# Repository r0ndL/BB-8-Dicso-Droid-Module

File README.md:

# BB-8-Dicso-Droid-Module
Released under CC4 SA NC BY Jim Yu

Disco-Droid 
Released under CC4 SA NC BY Jim Yu

#Introduction
The Disco Droid is an Arduino based module that will mainly provide Visual and Audio Effect for BB-8’s Dome. In order to create visual effects on the dome, more pins were needed that what an ordinary Arduino can provide, as such there was a need to create a module that has integrated output expander in order to accommodate the needs of the dome, and a few more extras for future upgrades. 
The Disco-Droid is capable working alone, or remotely controlled by another Bluetooth 4.0 LE device, it has a total of 32 12-bit PWM outputs, 7 spare analog pins from the Arduino, and 3 Digital I/O pins also from the Arduino, the Module has also integrated a MP3 Playback module that can drive a single 3W speaker. 

Most of all the different parts that was selected for this module has taken into account that many builders wish to make their domes as light as possible, in order to do so the Disco-Droid was design with the smallest off-the-shelf parts and modules in order to conserve on weight and size. The dimensions of the circuit board is just 2 x 3.5 x .7 inches, just slightly longer than your credit card. 

>Released under CC4 SA NC BY Jim Yu

#Roadmap
**V1.0.6 - Current Final Board Design for Version 1**
**Hardware Features**
- 32 PWM Output (Can handle Motors, LEDs, and Servos, etc..)
- 7 Analog Inputs (Can also be used for Digital Outputs)
- 3 Digital Outputs/Inputs
- 3W Speaker Output
- Bluetooth Ready
- Software Features
- Randomized Sound file playing
- 3 Pre-set Visualizer patterns 
- Small compact Code (using only 14% of the Arduino's memory, and 12% buffer memory)

**V1.1.6 - Same Board Design Utilizing Bluetooth remote connectivity**
**Hardware Features**
- Same as V1.0.6
- Software Features
- When left alone, it will follow V1.0.6 program functions
- Bluetooth Feature will be utilized to trigger the Dome light pattern changes, and sounds.

>In order to utilize V1.1.6 features a future Bluetooth Remote will be released to compliment the Disco-Droid Module.

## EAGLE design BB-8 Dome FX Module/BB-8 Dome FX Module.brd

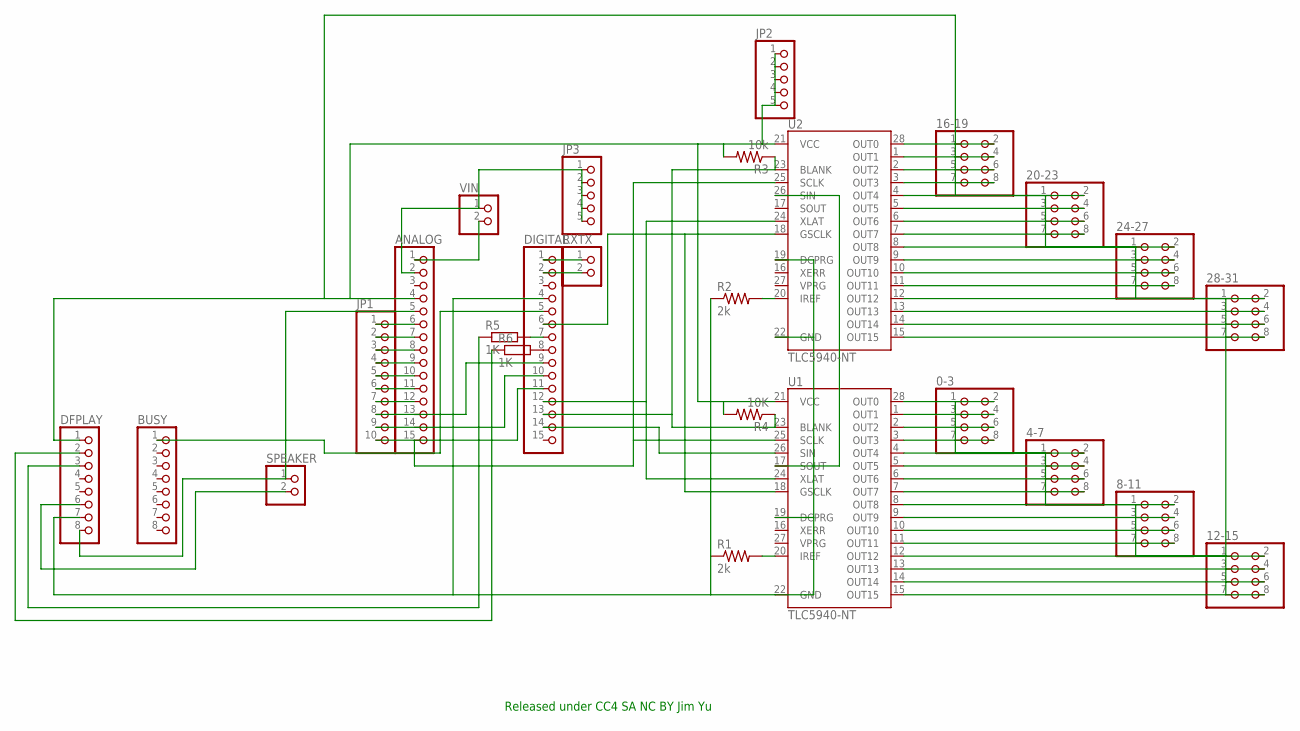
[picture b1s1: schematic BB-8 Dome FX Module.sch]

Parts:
0-3, 4-7, 8-11, 12-15, 16-19, 20-23, 24-27, 28-31: PINHD-2X4; 2X04
ANALOG: PINHD-1X15; 1X15
BUSY: PINHD-1X8; 1X08
DFPLAY: PINHD-1X8; 1X08
DIGITAL: PINHD-1X15; 1X15
JP1: PINHD-1X10; 1X10
JP2, JP3: PINHD-1X5; 1X05
R1, R2: 2k; 0204/5
R3: 10k; 0204/5
R4: 10K; 0204/5
R5, R6: 1K; 0204/5
RXTX: PINHD-1X2; 1X02
SPEAKER: PINHD-1X2; 1X02
U1, U2: TLC5940-NT; DIL28-3
VIN: PINHD-1X2; 1X02

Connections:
unnamed: DIGITAL.7, R5.2
unnamed: U1.17 (SOUT), U2.26 (SIN)
unnamed: DIGITAL.13, R3.1, R4.1, U1.23 (BLANK), U2.23 (BLANK)
unnamed: DIGITAL.12, U1.24 (XLAT), U2.24 (XLAT)
unnamed: DIGITAL.14, U1.26 (SIN)
unnamed: DIGITAL.6, U1.18 (GSCLK), U2.18 (GSCLK)
unnamed: ANALOG.15, U1.25 (SCLK), U2.25 (SCLK)
unnamed: DFPLAY.3, R5.1
unnamed: R2.2, U2.20 (IREF)
unnamed: R1.2, U1.20 (IREF)
unnamed: DFPLAY.2, R6.1
unnamed: DIGITAL.1, RXTX.1
unnamed: 16-19.4, U2.1 (OUT1)
unnamed: DIGITAL.2, RXTX.2
unnamed: 20-23.2, U2.4 (OUT4)
unnamed: 20-23.4, U2.5 (OUT5)
unnamed: 0-3.2, U1.28 (OUT0)
unnamed: 0-3.4, U1.1 (OUT1)
unnamed: 0-3.6, U1.2 (OUT2)
unnamed: 0-3.8, U1.3 (OUT3)
unnamed: 4-7.4, U1.5 (OUT5)
unnamed: 8-11.2, U1.8 (OUT8)
unnamed: 8-11.4, U1.9 (OUT9)
unnamed: 8-11.6, U1.10 (OUT10)
unnamed: 8-11.8, U1.11 (OUT11)
unnamed: 12-15.4, U1.13 (OUT13)
unnamed: 12-15.6, U1.14 (OUT14)
unnamed: 0-3.1, 0-3.3, 0-3.5, 0-3.7, 4-7.1, 4-7.3, 4-7.5, 4-7.7, 8-11.1, 8-11.3, 8-11.5, 8-11.7, 12-15.1, 12-15.3, 12-15.5, 12-15.7, 16-19.1, 16-19.3, 16-19.5, 16-19.7, 20-23.1, 20-23.3, 20-23.5, 20-23.7, 24-27.1, 24-27.3, 24-27.5, 24-27.7, 28-31.1, 28-31.3, 28-31.5, 28-31.7, ANALOG.4, DFPLAY.1, JP2.1, JP2.2, JP2.3, JP2.4, JP2.5, R3.2, R4.2, U1.21 (VCC), U2.21 (VCC)
unnamed: 12-15.8, U1.15 (OUT15)
unnamed: BUSY.1, DIGITAL.5
unnamed: ANALOG.5, DFPLAY.8, SPEAKER.1
unnamed: DFPLAY.6, SPEAKER.2
unnamed: DFPLAY.7, DIGITAL.4, R1.1, R2.1, U1.19 (DCPRG), U1.22 (GND), U2.19 (DCPRG), U2.22 (GND)
unnamed: DIGITAL.8, R6.2
unnamed: ANALOG.1, VIN.2
unnamed: ANALOG.2, JP3.1, JP3.2, JP3.3, JP3.4, JP3.5, VIN.1
unnamed: ANALOG.6, JP1.1
unnamed: ANALOG.7, JP1.2
unnamed: ANALOG.8, JP1.3
unnamed: ANALOG.9, JP1.4
unnamed: ANALOG.10, JP1.5
unnamed: ANALOG.11, JP1.6
unnamed: ANALOG.12, JP1.7
unnamed: DIGITAL.9, JP1.8
unnamed: DIGITAL.10, JP1.9
unnamed: DIGITAL.11, JP1.10
unnamed: 28-31.8, U2.15 (OUT15)
unnamed: 28-31.6, U2.14 (OUT14)
unnamed: 28-31.4, U2.13 (OUT13)
unnamed: 28-31.2, U2.12 (OUT12)
unnamed: 24-27.8, U2.11 (OUT11)
unnamed: 24-27.6, U2.10 (OUT10)
unnamed: 24-27.4, U2.9 (OUT9)
unnamed: 24-27.2, U2.8 (OUT8)
unnamed: 20-23.8, U2.7 (OUT7)
unnamed: 20-23.6, U2.6 (OUT6)
unnamed: 16-19.8, U2.3 (OUT3)
unnamed: 16-19.6, U2.2 (OUT2)
unnamed: 16-19.2, U2.28 (OUT0)
unnamed: 12-15.2, U1.12 (OUT12)
unnamed: 4-7.8, U1.7 (OUT7)
unnamed: 4-7.6, U1.6 (OUT6)
unnamed: 4-7.2, U1.4 (OUT4)

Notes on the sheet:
Released under CC4 SA NC BY Jim Yu

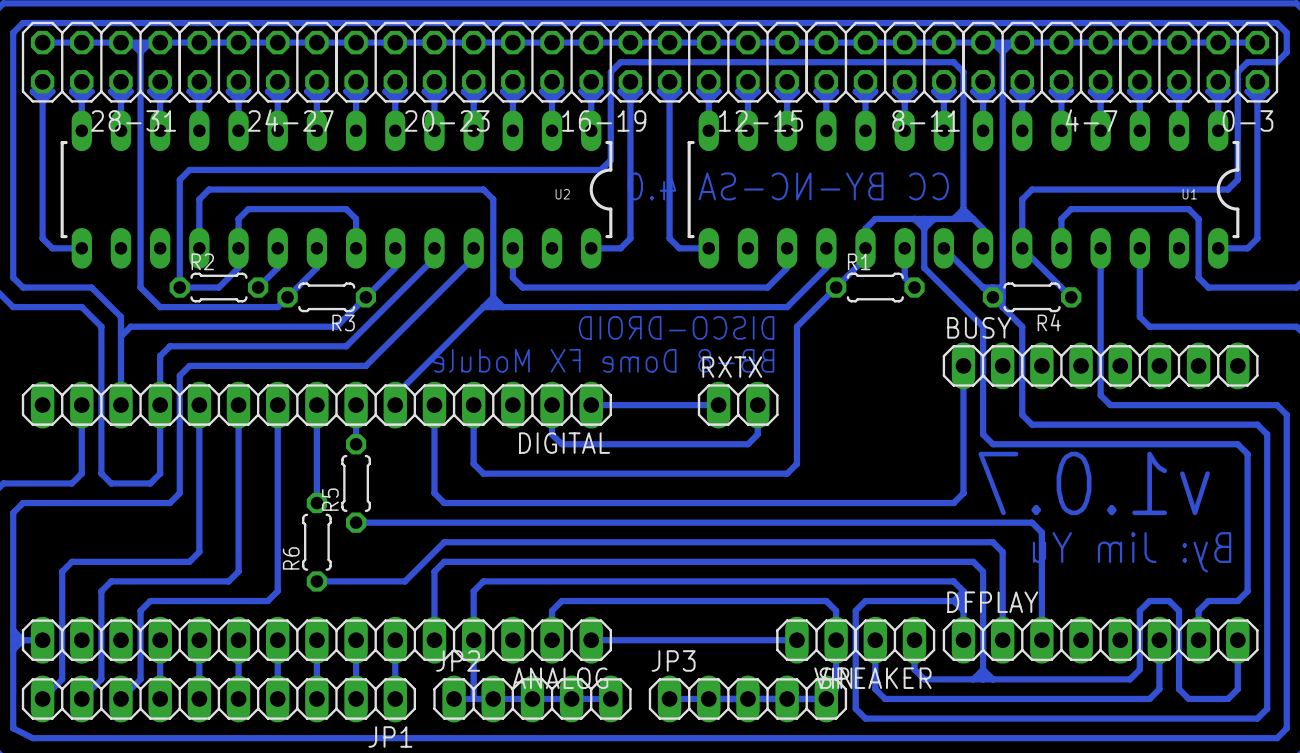
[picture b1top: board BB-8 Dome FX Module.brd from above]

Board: 2 copper layers, 26 parts (0 on the bottom side), 63 nets.

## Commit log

2016-02-01 BB-8 Disco Droid Module
    Bluetooth Ready BB-8 Dome FX Module - Released under CC4 SA NC BY Jim Yu

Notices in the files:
BB-8 Dome FX Module/BB-8 Dome FX Module.brd:
CC BY-NC-SA 4.0
parts and their libraries:
SparkFun-DigitalIC: Licensing: Creative Commons ShareAlike 4.0 International - https://creativecommons.org/licenses/by-sa/4.0
